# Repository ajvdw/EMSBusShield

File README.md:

# EMSBusShield

This board uses EMS-ESP32 with the following configuration

EMS-ESP32 (https://github.com/emsesp/EMS-ESP32)

Board Profile: Custom
Rx GPIO: 18
Tx GPIO: 19
Button GPIO: 0
Temperature GPIO: 0
Led GPIO: 2

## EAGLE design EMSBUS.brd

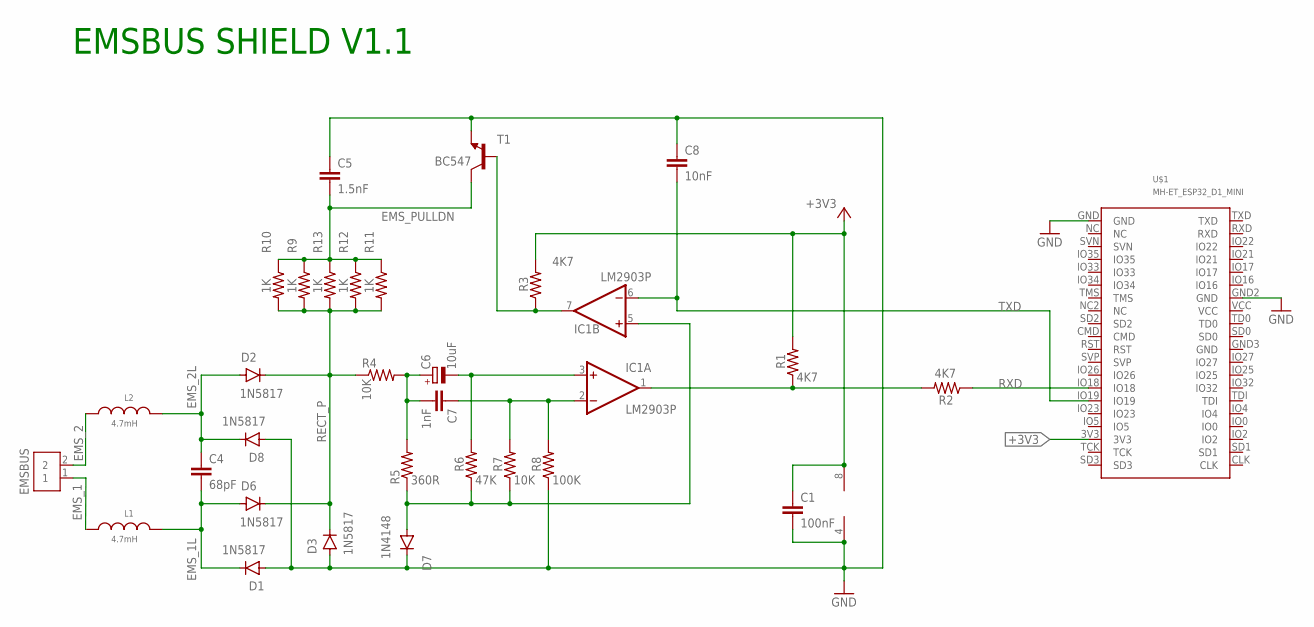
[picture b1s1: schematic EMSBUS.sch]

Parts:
C1: 100nF; CAP-PTH-2.54
C4: 68pF; CAP-PTH-2.54
C5: 1.5nF; CAP-PTH-2.54
C6: 10uF; E5-8,5
C7: 1nF; CAP-PTH-2.54
C8: 10nF; CAP-PTH-2.54
D1, D2, D3, D6, D8: 1N5817; DO-41
D7: 1N4148; DIODE-1N4148
EMSBUS: 2828XX-2282837-2; TERMBLK_508-2N
IC1: LM2903P; DIL08
L1, L2: 4.7mH; WE-FAMI_8010_744750230030
R1, R2, R3: 4K7; 0204/7
R4, R7: 10K; 0204/7
R5: 360R; 0204/7
R6: 47K; 0204/7
R8: 100K; 0204/7
R9, R10, R11, R12, R13: 1K; 0204/7
T1: BC547; TO92
U$1: MH-ET_ESP32_D1_MINI

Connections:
+3V3: C1.1, IC1.8 (V+), R1.2, R3.2, U$1.3V3
EMS_1: EMSBUS.1, L1.1
EMS_1L: C4.2, D1.C, D6.A, L1.2
EMS_2: EMSBUS.2, L2.1
EMS_2L: C4.1, D2.A, D8.C, L2.2
EMS_PULLDN: C5.2, R9.1, R10.1, R11.1, R12.1, R13.1, T1.3 (C)
GND: C1.2, C5.1, C8.1, D1.A, D3.A, D7.C, D8.A, IC1.4 (V-), R8.1, T1.1 (E), U$1.GND, U$1.GND2 (GND)
unnamed: IC1.7 (OUT), R3.1, T1.2 (B)
unnamed: IC1.1 (OUT), R1.1, R2.2
unnamed: D7.A, IC1.5 (+IN), R5.1, R6.1, R7.1
unnamed: C6.+, C7.2, R4.2, R5.2
unnamed: C7.1, IC1.2 (-IN), R7.2, R8.2
unnamed: C6.-, IC1.3 (+IN), R6.2
RECT_P: D2.C, D3.C, D6.C, R4.1, R9.2, R10.2, R11.2, R12.2, R13.2
RXD: R2.1, U$1.IO18
TXD: C8.2, IC1.6 (-IN), U$1.IO19

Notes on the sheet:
EMSBUS SHIELD V1.1

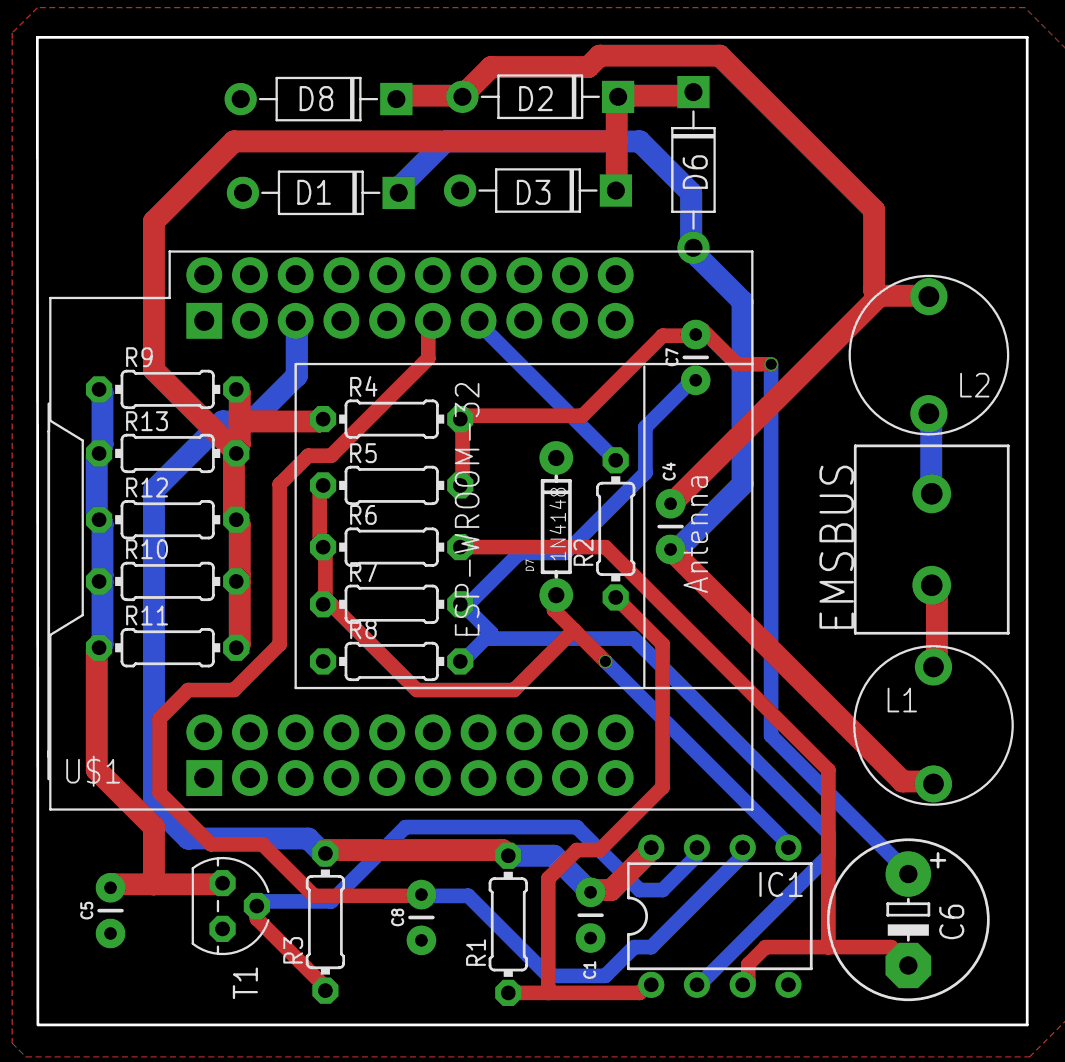
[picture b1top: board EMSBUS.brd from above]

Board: 2 copper layers, 55.0 x 54.9 mm, 31 parts (0 on the bottom side), 16 nets.

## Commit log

2022-08-01 Initial

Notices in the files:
parts and their libraries:
SparkFun-Capacitors: Licensing: Creative Commons ShareAlike 4.0 International - https://creativecommons.org/licenses/by-sa/4.0
Wurth_Elektronik_Passive_rev19e: Copyright: Würth Elektronik
